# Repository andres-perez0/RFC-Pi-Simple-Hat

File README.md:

# RFC-Pi-Simple-Hat
---
For the 2024-2025 season, the Notre Dame Robotic Football Club redesigned their PiHat to make it suitable for manufacturing.

## PCB Schematic:

## PCB Design: 

## Orthographic View:

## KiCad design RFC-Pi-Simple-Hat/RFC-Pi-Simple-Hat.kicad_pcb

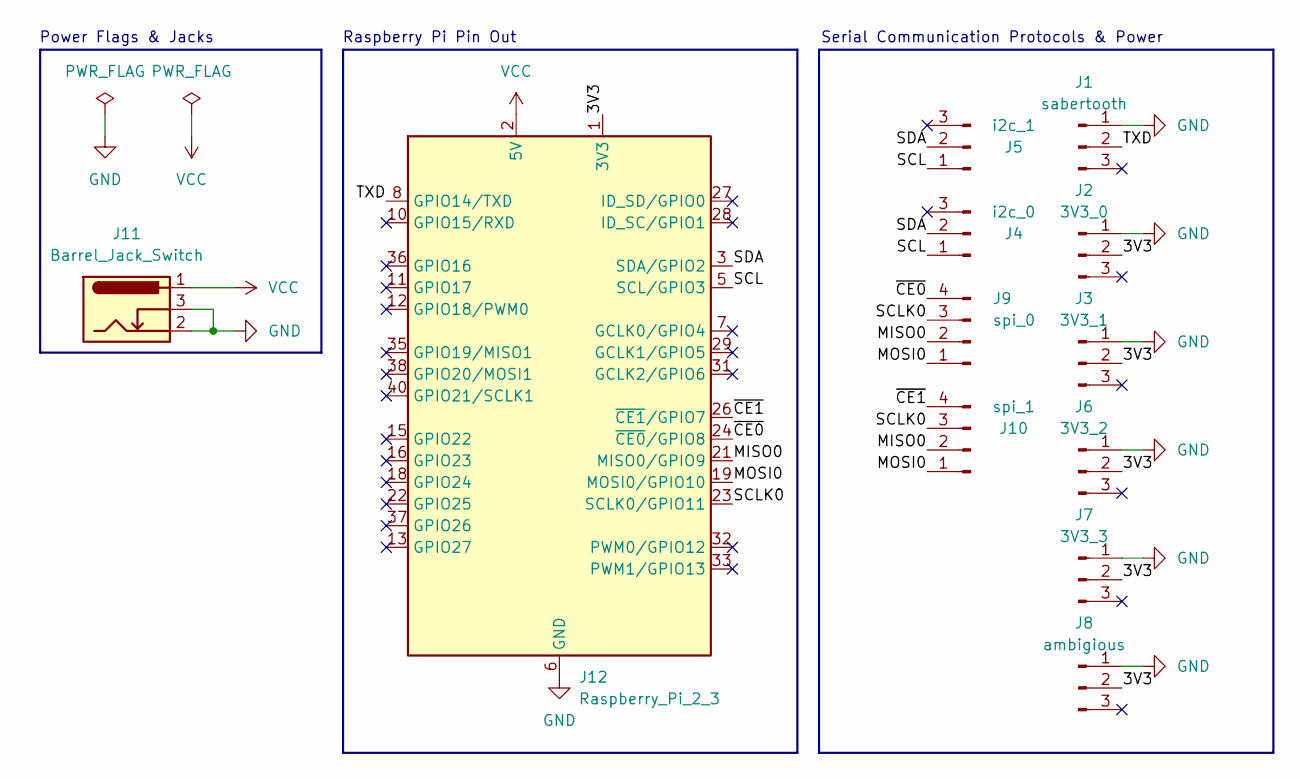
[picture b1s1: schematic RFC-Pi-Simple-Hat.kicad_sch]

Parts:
J1: sabertooth; Molex_KK-254_AE-6410-03A_1x03_P2.54mm_Vertical; LCSC Part # C234181
J2: 3V3_0; Molex_KK-254_AE-6410-03A_1x03_P2.54mm_Vertical; LCSC Part # C234181
J3: 3V3_1; Molex_KK-254_AE-6410-03A_1x03_P2.54mm_Vertical; LCSC Part # C234181
J4: i2c_0; Molex_KK-254_AE-6410-03A_1x03_P2.54mm_Vertical; LCSC Part # C234181
J5: i2c_1; Molex_KK-254_AE-6410-03A_1x03_P2.54mm_Vertical; LCSC Part # C234181
J6: 3V3_2; Molex_KK-254_AE-6410-03A_1x03_P2.54mm_Vertical; LCSC Part # C234181
J7: 3V3_3; Molex_KK-254_AE-6410-03A_1x03_P2.54mm_Vertical; LCSC Part # C234181
J8: ambigious; Molex_KK-254_AE-6410-03A_1x03_P2.54mm_Vertical; LCSC Part # C234181
J9: spi_0; Molex_KK-254_AE-6410-04A_1x04_P2.54mm_Vertical; LCSC Part # C164168
J10: spi_1; Molex_KK-254_AE-6410-04A_1x04_P2.54mm_Vertical; LCSC Part # C164168
J11: Barrel_Jack_Switch; NINIGI_DC-005; LCSC Part # C130239
J12: Raspberry_Pi_2_3; PinHeader_2x20_P2.54mm_Vertical; LCSC Part # C132132

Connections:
/3V3: J2.2, J3.2, J6.2, J7.2, J8.2, J12.1 (3V3), J12.17 (3V3)
/MISO0: J9.2, J10.2, J12.21 (MISO0/GPIO9)
/MOSI0: J9.1, J10.1, J12.19 (MOSI0/GPIO10)
/SCL: J4.1, J5.1, J12.5 (SCL/GPIO3)
/SCLK0: J9.3, J10.3, J12.23 (SCLK0/GPIO11)
/SDA: J4.2, J5.2, J12.3 (SDA/GPIO2)
/TXD: J1.2, J12.8 (GPIO14/TXD)
/~CE0: J9.4, J12.24 (~CE0/GPIO8)
/~CE1: J10.4, J12.26 (~CE1/GPIO7)
GND: J1.1, J2.1, J3.1, J6.1, J7.1, J8.1, J11.2, J11.3, J12.6 (GND), J12.9 (GND), J12.14 (GND), J12.20 (GND), J12.25 (GND), J12.30 (GND), J12.34 (GND), J12.39 (GND)
VCC: J11.1, J12.2 (5V), J12.4 (5V)

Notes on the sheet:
Power Flags & Jacks
Raspberry Pi Pin Out
Serial Communication Protocols & Power

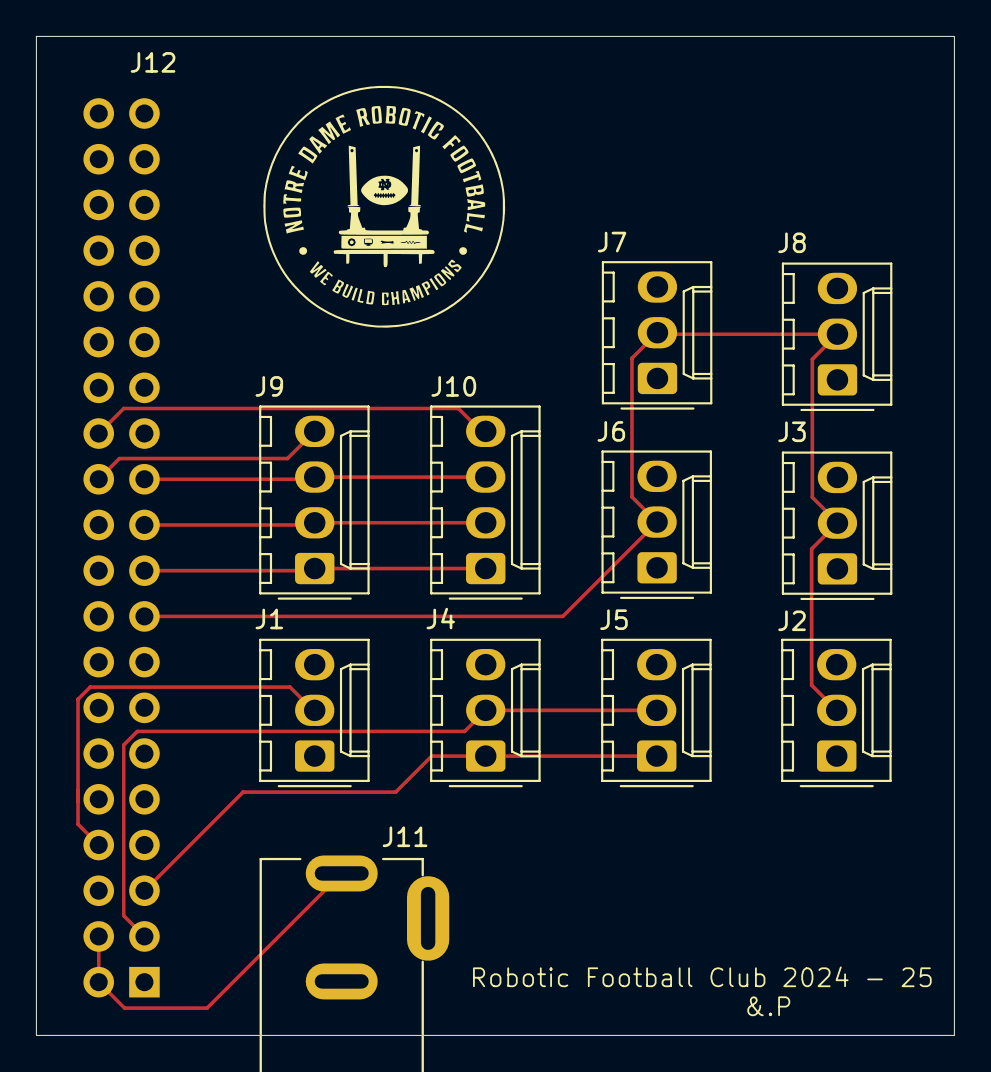
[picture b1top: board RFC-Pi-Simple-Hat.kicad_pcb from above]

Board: 2 copper layers, 51.0 x 55.5 mm, 12 parts (1 on the bottom side), 11 nets.

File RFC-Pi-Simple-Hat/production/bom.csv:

Designator,Footprint,Quantity,Value,LCSC Part #
J1,Molex_KK-254_AE-6410-03A_1x03_P2.54mm_Vertical,1,sabertooth,C234181
J10,Molex_KK-254_AE-6410-04A_1x04_P2.54mm_Vertical,1,spi_1,C164168
J11,NINIGI_DC-005,1,Barrel_Jack_Switch,C130239
J12,PinHeader_2x20_P2.54mm_Vertical,1,Raspberry_Pi_2_3,C132132
J2,Molex_KK-254_AE-6410-03A_1x03_P2.54mm_Vertical,1,3V3_0,C234181
J3,Molex_KK-254_AE-6410-03A_1x03_P2.54mm_Vertical,1,3V3_1,C234181
J4,Molex_KK-254_AE-6410-03A_1x03_P2.54mm_Vertical,1,i2c_0,C234181
J5,Molex_KK-254_AE-6410-03A_1x03_P2.54mm_Vertical,1,i2c_1,C234181
J6,Molex_KK-254_AE-6410-03A_1x03_P2.54mm_Vertical,1,3V3_2,C234181
J7,Molex_KK-254_AE-6410-03A_1x03_P2.54mm_Vertical,1,3V3_3,C234181
J8,Molex_KK-254_AE-6410-03A_1x03_P2.54mm_Vertical,1,ambigious,C234181
J9,Molex_KK-254_AE-6410-04A_1x04_P2.54mm_Vertical,1,spi_0,C164168

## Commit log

2025-01-08 Pushes Current Iteration of PiHat
2025-01-15 Updated board
